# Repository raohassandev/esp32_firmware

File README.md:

# Automatrix ESP32 PV-DG Controller

Compact ESP-IDF firmware for the ESP32-S3 PV-DG controller.

## Current scope

- Grid and generator meter polling through Modbus TCP or an RTU gateway.
- Up to twelve configurable inverter channels.
- Multi-brand inverter profile catalogue with fail-closed production write qualification.
- Periodic inverter identity, active-power and command-readback telemetry.
- SolTrix Modbus TCP simulator tests for Huawei, GoodWe and Solis synthetic profiles.
- Automatic removal of stale/offline inverter capacity.
- Lightweight embedded commissioning interface.
- Persistent light and dark UI themes.
- JSON configuration import and export.

Simulator-only profiles and pending manufacturer profiles cannot issue production writes. Physical automatic inverter control remains locked until exact manuals and hardware qualification are complete.

## Rev-A hardware / PCB planning

The canonical single-PCB hardware plan is now maintained in:

- [`docs/HARDWARE_PCB_REVA_MASTER_PLAN.md`](docs/HARDWARE_PCB_REVA_MASTER_PLAN.md) — PCB architecture, mandatory/optional functions, relay outputs, GPIO allocation, validation gates and DIN-rail enclosure plan.
- [`docs/PCB_AND_ENCLOSURE_SERVICE_PROVIDER_RFQ.md`](docs/PCB_AND_ENCLOSURE_SERVICE_PROVIDER_RFQ.md) — quotation package for PCB design, prototype/production PCBA and enclosure/casing service providers.

The Rev-A mandatory hardware baseline is ESP32-S3 + wired Ethernet + two independent RS485 ports + four dry-contact relay outputs + serial touch-display UART + USB-C + 12/24 VDC power. Four isolated digital inputs, RTC, microSD and an RS232 HMI option are planned as optional/DNP sections on the same PCB.

## Pull the current integration branch

Run in an ESP-IDF Command Prompt from the local repository directory:

```bash
git fetch origin
git switch feature/multibrand-inverter-profiles
git pull --ff-only origin feature/multibrand-inverter-profiles
git rev-parse HEAD
```

## Build and flash

Replace `COM5` with the board's actual serial port:

```bash
idf.py set-target esp32s3
idf.py -p COM5 build flash monitor
```

Normal `flash` preserves the NVS configuration partition. Do not run `erase-flash` unless a destructive reset is intentionally required.

To exit the serial monitor, press `Ctrl+]`.

## One-line Windows command

Replace the repository path and COM port:

```bat
cd /d C:\path\to\esp32_firmware && git fetch origin && git switch feature/multibrand-inverter-profiles && git pull --ff-only origin feature/multibrand-inverter-profiles && git rev-parse HEAD && idf.py set-target esp32s3 && idf.py -p COM5 build flash monitor
```

## Theme control

The sun/moon button in the top bar switches between light and dark themes. The selection is stored in the browser. On first use, the interface follows the operating-system color preference.

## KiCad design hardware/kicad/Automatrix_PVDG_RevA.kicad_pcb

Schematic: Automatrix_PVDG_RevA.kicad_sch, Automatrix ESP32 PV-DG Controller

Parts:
BT1: CR1220; BatteryHolder_Keystone_3000_1x12mm; not fitted
C1, C4, C6: 0.1uF 50V; C_0603_1608Metric
C2, C34: 6.8nF; C_0603_1608Metric
C3: 39pF; C_0603_1608Metric
C5: 10uF 35V; C_1206_3216Metric
C7, C8: 22uF 25V; C_1206_3216Metric
C9: 100pF; C_0603_1608Metric
C10: 1uF; C_0603_1608Metric
C11: 10uF; C_0805_2012Metric
C12, C26, C27, C28, C29, C30, C31, C36, C37: 0.1uF; C_0603_1608Metric
C13: 4.7uF; C_0805_2012Metric
C14: 10nF; C_0603_1608Metric
C15, C16: 18pF; C_0603_1608Metric
C17: 10uF; C_0805_2012Metric; not fitted
C18: 0.1uF; C_0603_1608Metric; not fitted
C19, C20: 22pF DNP; C_0603_1608Metric; not fitted
C21, C22, C23, C24, C25: 0.1uF DNP; C_0603_1608Metric; not fitted
C32: 10uF 10V; C_0805_2012Metric
C33: 22nF; C_0603_1608Metric
C35: 1nF 2kV; R_0805_2012Metric
CIN1, CIN2: Murata GRM32ER72A225KA35L 2.2uF 100V X7R; C_1210_3225Metric
CINB1: 100uF 50V; CP_Radial_D10.0mm_P5.00mm
COUT1, COUT2: Murata GRM32ER61A476KE20L 47uF 10V X5R; C_1210_3225Metric
COUT3: 0.1uF; C_0603_1608Metric
D1, D2: TPD1E05U06DYAR; D_SOD-523
D3, D4: SS34; D_SMA
D5, D6: SM712; SOT-23
D7, D9, D11, D13: SS14; D_SMA
D8: RELAY1; LED_0805_2012Metric
D10: RELAY2; LED_0805_2012Metric
D12: RELAY3; LED_0805_2012Metric
D14: RELAY4; LED_0805_2012Metric
D15, D16, D17, D18: 1N4148 reverse; D_SOD-123; not fitted
D19, D20: BAT54; D_SOD-323; not fitted
D21: TPD1E10B06DYAR; D_SOD-523
D22, D24: AMBER 150080AS75000; LED_0805_2012Metric
D23, D25: GREEN 150080VS75000; LED_0805_2012Metric
D26: BRIGHT GREEN 150080VS75000; LED_0805_2012Metric
D27: RED 150080RS75000; LED_0805_2012Metric
DTVS1: SMBJ33A; D_SMA
DZREV1: 12V gate clamp; D_SOD-123
F1: 3.15A 60V+; Fuse_1206_3216Metric
F2: 1.1A PTC; Fuse_1206_3216Metric
FB1: 600R@100MHz >=1A; R_0805_2012Metric
J1: Same Sky TB007-508-02BE; TerminalBlock_CUI_TB007-508-02_1x02_P5.08mm_Horizontal
J2: GCT USB4105-GF-A-120; USB_C_Receptacle_GCT_USB4105-xx-A_16P_TopMnt_Horizontal
J3: J1B1211CCD; RJ45_Cetus_J1B1211CCD_Horizontal
J4, J5: Same Sky TB007-508-03BE; TerminalBlock_CUI_TB007-508-03_1x03_P5.08mm_Horizontal
J6: HMI +5/GND/TX/RX; JST_XH_B4B-XH-A_1x04_P2.50mm_Vertical
J7, J8, J9, J10: Phoenix MKDS 3/3-5.08 BK 1712193; TerminalBlock_Phoenix_MKDS-3-3-5.08_1x03_P5.08mm_Horizontal
J11: Same Sky TB007-508-05BE DNP; TerminalBlock_CUI_TB007-508-05_1x05_P5.08mm_Horizontal; not fitted
J12: microSD DNP; microSD_HC_Hirose_DM3AT-SF-PEJM5; not fitted
J13: RS232 GND/TX/RX DNP; JST_XH_B3B-XH-A_1x03_P2.50mm_Vertical; not fitted
K1, K2, K3, K4: HF3FF/005-1ZST; Relay_SPDT_Hongfa_JQC-3FF_0XX-1Z
L1: Wurth 744393465082 8.2uH; L_Wuerth_XHMI-6060
L2: 6.8uH 5A; L_Wuerth_XHMI-6060
Q1, Q2, Q3, Q4: AOS AO3400A; SOT-23
QREV1: DMP6023LSS; SO-8_3.9x4.9mm_P1.27mm
R1: 523k; R_0603_1608Metric
R2: 84.5k; R_0603_1608Metric
R3: 162k; R_0603_1608Metric
R4: 53.6k; R_0603_1608Metric
R5: 10.2k; R_0603_1608Metric
R6: 13k; R_0603_1608Metric
R7, R8: 5.1k; R_0603_1608Metric
R9, R10, R13, R14, R15, R16, R20, R26, R29, R32, R35: 10k; R_0603_1608Metric
R11: 12.4k 1%; R_0603_1608Metric
R12: 1M; R_0603_1608Metric
R17, R21: 120R DNP; R_1206_3216Metric; not fitted
R18, R19, R22, R23: 680R DNP; R_0603_1608Metric; not fitted
R24, R25, R28, R31, R34: 100R; R_0603_1608Metric
R27, R30, R33, R36: 1k; R_0603_1608Metric
R37, R39, R41, R43: 3.3k 0.25W; R_1206_3216Metric; not fitted
R38, R40, R42, R44, R47, R48, R49, R50: 10k; R_0603_1608Metric; not fitted
R45, R46: 4.7k; R_0603_1608Metric; not fitted
R51, R52: 27R; R_0603_1608Metric
R53, R54, R55, R56: 0R; R_0603_1608Metric
R57, R58, R59, R60: 49.9R 1%; R_0603_1608Metric
R61: 10R 1%; R_0603_1608Metric
R62, R63: 330R; R_0603_1608Metric
R64, R65, R66, R67, R70, R71: 680R; R_0603_1608Metric
R68, R69: 100k; R_0603_1608Metric
RREV1: 100k; R_0603_1608Metric
SW1: RESET; Panasonic_EVQPUJ_EVQPUA
SW2: BOOT; Panasonic_EVQPUJ_EVQPUA
U1: ESP32-S3-WROOM-1-N8; ESP32-S3-WROOM-1
U2: W5500; LQFP-48_7x7mm_P0.5mm
U3, U4: THVD1410D; SOIC-8_3.9x4.9mm_P1.27mm
U5: TPS54360B; TI_SO-PowerPAD-8_ThermalVias
U6: AP63203WU-7; TSOT-23-6
U7: MAX3232 DNP; SOIC-16_3.9x9.9mm_P1.27mm; not fitted
U8, U9, U10, U11: LTV-817; DIP-4_W7.62mm; not fitted
U12: PCF8563T DNP; SOIC-8_3.9x4.9mm_P1.27mm; not fitted
U13: SN74LVC1G17DBVR; SOT-23-5
U14: SN74LVC14APWR; TSSOP-14_4.4x5mm_P0.65mm
Y1: Abracon ABM8-25.000MHZ-D2Y-T 25MHz; Crystal_SMD_3225-4Pin_3.2x2.5mm
Y2: 32.768kHz; Crystal_SMD_3215-2Pin_3.2x1.5mm; not fitted

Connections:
3V3: C7.1 (+), C8.1 (+), C9.1, C11.1 (+), C12.1, C17.1 (+), C18.1, C25.1, C36.1, C37.1, D19.2 (A), D26.2 (A), D27.2 (A), FB1.1, J3.10 (GRN+), J3.12 (YLW+), J12.4 (VDD), L2.2, R9.1, R10.1, R13.1, R14.1, R15.1, R18.1, R22.1, R38.1, R40.1, R42.1, R44.1, R45.1, R46.1, R47.1, R48.1, R49.1, R50.1, U1.2 (3V3), U2.28 (VDD), U3.8 (VCC), U4.8 (VCC), U6.1 (FB), U7.16 (VCC), U13.5 (VCC), U14.14 (VCC)
3V3A: C26.1, C27.1, C28.1, C29.1, C30.1, C31.1, C32.1, FB1.2, R57.1, R58.1, R59.1, R60.1, R61.1, U2.4 (AVDD), U2.8 (AVDD), U2.11 (AVDD), U2.15 (AVDD), U2.17 (AVDD), U2.21 (AVDD)
5V_FIELD: COUT1.1 (+), COUT2.1 (+), COUT3.1, D3.2 (A), D7.1 (K), D9.1 (K), D11.1 (K), D13.1 (K), F2.1, K1.A1 (COIL_A), K2.A1 (COIL_A), K3.A1 (COIL_A), K4.A1 (COIL_A), L1.2, R4.1, R27.1, R30.1, R33.1, R36.1
5V_HMI: F2.2, J6.1
5V_LOGIC_IN: C5.1 (+), C6.1, D3.1 (K), D4.1 (K), U6.2 (EN), U6.3 (VIN)
BUCK3_BST: C4.1, U6.6 (BST)
BUCK3_SW: C4.2, L2.1, U6.5 (SW)
BUCK_BOOT: C1.1, U5.1 (BOOT)
BUCK_COMP: C3.1, R6.1, U5.6 (COMP)
BUCK_COMP_RC: C2.1, R6.2
BUCK_EN: R1.2, R2.1, U5.3 (EN)
BUCK_FB: R4.2, R5.1, U5.5 (FB)
BUCK_RT: R3.1, U5.4 (RT_CLK)
BUCK_SW: C1.2, L1.1, U5.8 (SW)
CHASSIS: C35.2, J2.SH (SHIELD), J3.8 (GHs_GND), J3.13 (CH_GND)
DI1_FIELD: J11.1, R37.1
DI1_LEDK: D15.1 (K), R37.2, U8.1 (A)
DI1_LOGIC: R38.2, U1.39 (IO1), U8.4 (C)
DI2_FIELD: J11.2, R39.1
DI2_LEDK: D16.1 (K), R39.2, U9.1 (A)
DI2_LOGIC: R40.2, U1.38 (IO2), U9.4 (C)
DI3_FIELD: J11.3, R41.1
DI3_LEDK: D17.1 (K), R41.2, U10.1 (A)
DI3_LOGIC: R42.2, U1.24 (IO47), U10.4 (C)
DI4_FIELD: J11.4, R43.1
DI4_LEDK: D18.1 (K), R43.2, U11.1 (A)
DI4_LOGIC: R44.2, U1.25 (IO48), U11.4 (C)
DIAG_A_RX_DRV: R65.1, U14.4 (2Y)
DIAG_A_TX_DRV: R64.1, U14.2 (1Y)
DIAG_B_RX_DRV: R67.1, U14.8 (4Y)
DIAG_B_TX_DRV: R66.1, U14.6 (3Y)
DI_COM: D15.2 (A), D16.2 (A), D17.2 (A), D18.2 (A), J11.5, U8.2 (K), U9.2 (K), U10.2 (K), U11.2 (K)
ESP_BOOT: R10.2, SW2.1, U1.27 (IO0)
ESP_EN: C10.1, R9.2, SW1.1, U1.3 (EN)
ETH_1V2: C14.1, U2.22 (1V2O)
ETH_CS: U1.18 (IO10), U2.32 (SCSn)
ETH_EXRES: R11.1, U2.10 (EXRES1)
ETH_INT: U1.17 (IO9), U2.36 (INTn)
ETH_LED_ACT: R63.1, U2.27 (ACTLED)
ETH_LED_ACT_K: J3.11 (YLW-), R63.2
ETH_LED_LINK: R62.1, U2.25 (LINKLED)
ETH_LED_LINK_K: J3.9 (GRN-), R62.2
ETH_MISO: U1.21 (IO13), U2.34 (MISO)
ETH_MOSI: U1.19 (IO11), U2.35 (MOSI)
ETH_PMODE0: R15.2, U2.45 (PMODE0)
ETH_PMODE1: R14.2, U2.44 (PMODE1)
ETH_PMODE2: R13.2, U2.43 (PMODE2)
ETH_RCT: C34.1, J3.5 (RCT)
ETH_RST: U1.12 (IO8), U2.37 (RSTn)
ETH_RXN: R56.1, U2.5 (RXN)
ETH_RXN_MAG: J3.6 (RD-), R56.2, R60.2
ETH_RXP: R55.1, U2.6 (RXP)
ETH_RXP_MAG: J3.4 (RD+), R55.2, R59.2
ETH_SCLK: U1.20 (IO12), U2.33 (SCLK)
ETH_TCT: C33.1, J3.2 (TCT), R61.2
ETH_TOCAP: C13.1 (+), U2.20 (TOCAP)
ETH_TXN: R54.1, U2.1 (TXN)
ETH_TXN_MAG: J3.3 (TD-), R54.2, R58.2
ETH_TXP: R53.1, U2.2 (TXP)
ETH_TXP_MAG: J3.1 (TD+), R53.2, R57.2
ETH_XI: C15.1, R12.1, U2.30 (XI_CLKIN), Y1.1
ETH_XO: C16.1, R12.2, U2.31 (XO), Y1.2
GND: BT1.2 (-), C2.2, C3.2, C5.2 (-), C6.2, C7.2 (-), C8.2 (-), C9.2, C10.2, C11.2 (-), C12.2, C13.2 (-), C14.2, C15.2, C16.2, C17.2 (-), C18.2, C19.2, C20.2, C23.2, C24.2, C25.2, C26.2, C27.2, C28.2, C29.2, C30.2, C31.2, C32.2, C33.2, C34.2, C35.1, C36.2, C37.2, CIN1.2 (-), CIN2.2 (-), CINB1.2 (-), COUT1.2 (-), COUT2.2 (-), COUT3.2, D1.2 (GND), D2.2 (GND), D21.2 (GND), D22.1 (K), D23.1 (K), D24.1 (K), D25.1 (K), DTVS1.2 (K), J1.2, J2.A1 (GND_A1), J2.A12 (GND_A12), J2.B1 (GND_B1), J2.B12 (GND_B12), J4.3, J5.3, J6.2, J12.6 (GND), J12.9 (SHIELD), J13.1, Q1.2 (S), Q2.2 (S), Q3.2 (S), Q4.2 (S), R2.2, R3.2, R5.2, R7.2, R8.2, R11.2, R16.2, R19.2, R20.2, R23.2, R26.2, R29.2, R32.2, R35.2, R68.2, R69.2, RREV1.2, SW1.2, SW2.2, U1.1 (GND), U1.40 (GND), U1.41 (EPAD), U2.3 (AGND), U2.9 (AGND), U2.14 (AGND), U2.16 (AGND), U2.19 (AGND), U2.23 (RSVD_GND), U2.29 (GND), U2.48 (AGND), U3.5 (GND), U4.5 (GND), U5.7 (GND), U5.9 (PAD), U6.4 (GND), U7.15 (GND), U8.3 (E), U9.3 (E), U10.3 (E), U11.3 (E), U12.4 (VSS), U13.3 (GND), U14.7 (GND)
HMI_RS232_RX: J13.3, U7.13 (R1IN)
HMI_RS232_TX: J13.2, U7.14 (T1OUT)
HMI_RX: U1.22 (IO14), U7.12 (R1OUT), U13.4 (Y)
HMI_RX_IN: D21.1 (IO), J6.4, U13.2 (A)
HMI_TX: R24.1, U1.8 (IO15), U7.11 (T1IN)
HMI_TX_OUT: J6.3, R24.2
LED_A_RX_A: D23.2 (A), R65.2
LED_A_TX_A: D22.2 (A), R64.2
LED_B_RX_A: D25.2 (A), R67.2
LED_B_TX_A: D24.2 (A), R66.2
RELAY1_COIL: D7.2 (A), D8.1 (K), K1.A2 (COIL_B), Q1.3 (D)
RELAY1_CTL: R25.1, U1.4 (IO4)
RELAY1_GATE: Q1.1 (G), R25.2, R26.1
RELAY2_COIL: D9.2 (A), D10.1 (K), K2.A2 (COIL_B), Q2.3 (D)
RELAY2_CTL: R28.1, U1.5 (IO5)
RELAY2_GATE: Q2.1 (G), R28.2, R29.1
RELAY3_COIL: D11.2 (A), D12.1 (K), K3.A2 (COIL_B), Q3.3 (D)
RELAY3_CTL: R31.1, U1.6 (IO6)
RELAY3_GATE: Q3.1 (G), R31.2, R32.1
RELAY4_COIL: D13.2 (A), D14.1 (K), K4.A2 (COIL_B), Q4.3 (D)
RELAY4_CTL: R34.1, U1.7 (IO7)
RELAY4_GATE: Q4.1 (G), R34.2, R35.1
REV_GATE: DZREV1.2 (A), QREV1.1 (G), RREV1.1
RLY1_COM: J7.2, K1.11 (COM)
RLY1_LED_A: D8.2 (A), R27.2
RLY1_NC: J7.1, K1.12 (NC)
RLY1_NO: J7.3, K1.14 (NO)
RLY2_COM: J8.2, K2.11 (COM)
RLY2_LED_A: D10.2 (A), R30.2
RLY2_NC: J8.1, K2.12 (NC)
RLY2_NO: J8.3, K2.14 (NO)
RLY3_COM: J9.2, K3.11 (COM)
RLY3_LED_A: D12.2 (A), R33.2
RLY3_NC: J9.1, K3.12 (NC)
RLY3_NO: J9.3, K3.14 (NO)
RLY4_COM: J10.2, K4.11 (COM)
RLY4_LED_A: D14.2 (A), R36.2
RLY4_NC: J10.1, K4.12 (NC)
RLY4_NO: J10.3, K4.14 (NO)
RS232_C1M: C21.2, U7.3 (C1-)
RS232_C1P: C21.1, U7.1 (C1+)
RS232_C2M: C22.2, U7.5 (C2-)
RS232_C2P: C22.1, U7.4 (C2+)
RS232_VMINUS: C24.1, U7.6 (V-)
RS232_VPLUS: C23.1, U7.2 (V+)
RS485A_A: D5.1 (A), J4.1, R17.1, R18.2, U3.6 (A)
RS485A_B: D5.2 (K), J4.2, R17.2, R19.1, U3.7 (B)
RS485A_DE: R16.1, U1.35 (IO42), U3.2 (REn), U3.3 (DE)
RS485A_RX: U1.36 (IO44), U3.1 (R), U14.3 (2A)
RS485A_TX: U1.37 (IO43), U3.4 (D), U14.1 (1A)
RS485B_A: D6.1 (A), J5.1, R21.1, R22.2, U4.6 (A)
RS485B_B: D6.2 (K), J5.2, R21.2, R23.1, U4.7 (B)
RS485B_DE: R20.1, U1.9 (IO16), U4.2 (REn), U4.3 (DE)
RS485B_RX: U1.11 (IO18), U4.1 (R), U14.9 (4A)
RS485B_TX: U1.10 (IO17), U4.4 (D), U14.5 (3A)
RTC_BAT: BT1.1 (+), D20.2 (A)
RTC_SCL: R46.2, U1.32 (IO39), U12.6 (SCL)
RTC_SDA: R45.2, U1.31 (IO38), U12.5 (SDA)
RTC_VDD: D19.1 (K), D20.1 (K), U12.8 (VDD)
RTC_X1: U12.1 (OSCI), Y2.1
RTC_X2: U12.2 (OSCO), Y2.2
SD_CS: J12.2 (CS_DAT3), R47.2, U1.29 (IO36)
SD_MISO: J12.7 (MISO_DAT0), R50.2, U1.30 (IO37)
SD_MOSI: J12.3 (MOSI_CMD), R48.2, U1.34 (IO41)
SD_SCLK: J12.5 (SCLK), R49.2, U1.33 (IO40)
STATUS_ALERT_CTL: R69.1, U1.23 (IO21), U14.13 (6A)
STATUS_GREEN_DRV: R70.1, U14.10 (5Y)
STATUS_GREEN_K: D26.1 (K), R70.2
STATUS_LED_CTL: R68.1, U1.28 (IO35), U14.11 (5A)
STATUS_RED_DRV: R71.1, U14.12 (6Y)
STATUS_RED_K: D27.1 (K), R71.2
USB_5V: D4.2 (A), J2.A4 (VBUS_A4), J2.A9 (VBUS_A9), J2.B4 (VBUS_B4), J2.B9 (VBUS_B9)
USB_CC1: J2.A5 (CC1), R7.1
USB_CC2: J2.B5 (CC2), R8.1
USB_D+: D2.1 (IO), J2.A6 (D+_A6), J2.B6 (D+_B6), R52.2
USB_D+_MCU: C20.1, R52.1, U1.14 (IO20)
USB_D-: D1.1 (IO), J2.A7 (D-_A7), J2.B7 (D-_B7), R51.2
USB_D-_MCU: C19.1, R51.1, U1.13 (IO19)
VIN_FUSED: F1.2, QREV1.3 (D)
VIN_PROTECTED: CIN1.1 (+), CIN2.1 (+), CINB1.1 (+), DTVS1.1 (A), DZREV1.1 (K), QREV1.2 (S), R1.1, U5.2 (VIN)
VIN_RAW: F1.1, J1.1

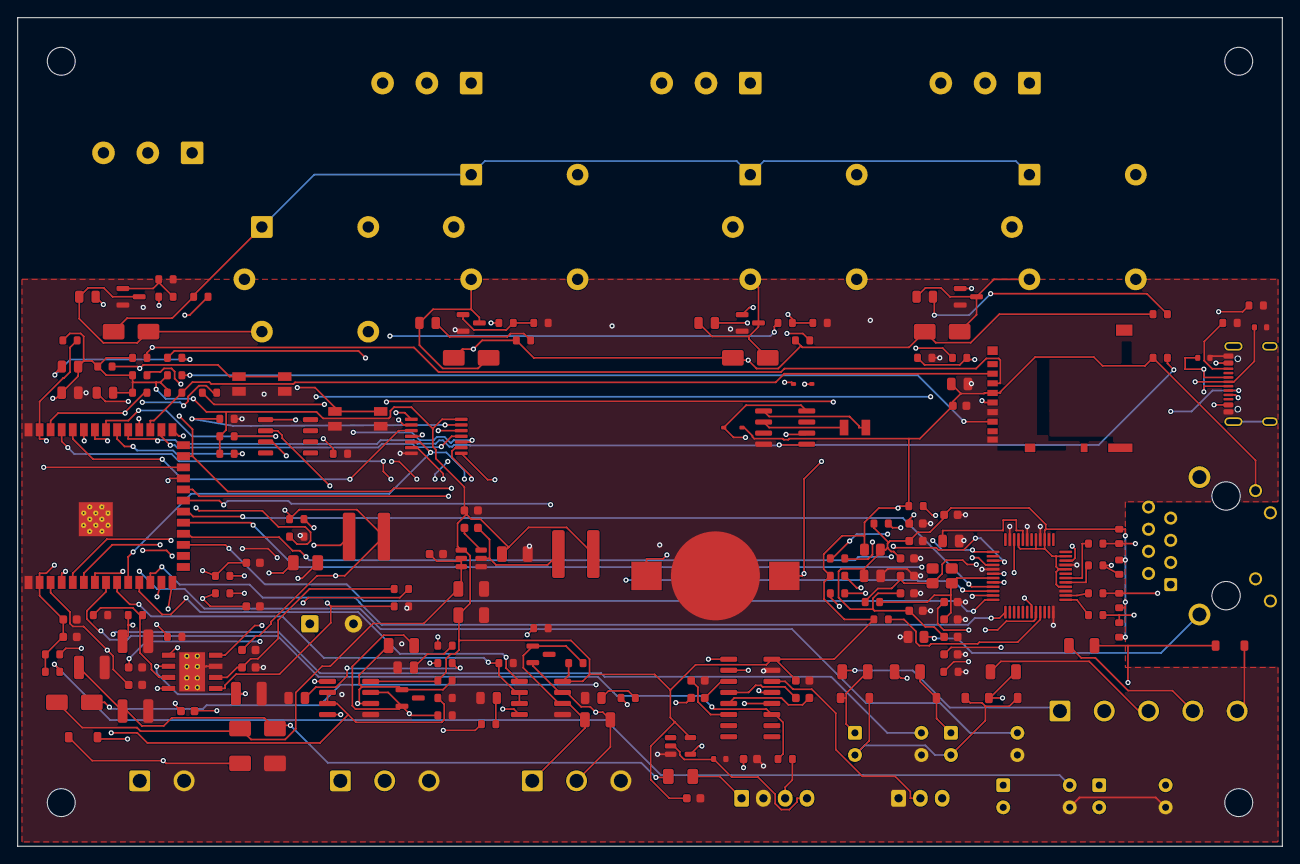
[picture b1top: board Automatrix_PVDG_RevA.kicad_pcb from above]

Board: 4 copper layers, 145.0 x 95.0 mm, 194 parts (0 on the bottom side), 144 nets.

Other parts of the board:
H1, H2, H3, H4: M3; MountingHole_3.2mm_M3
